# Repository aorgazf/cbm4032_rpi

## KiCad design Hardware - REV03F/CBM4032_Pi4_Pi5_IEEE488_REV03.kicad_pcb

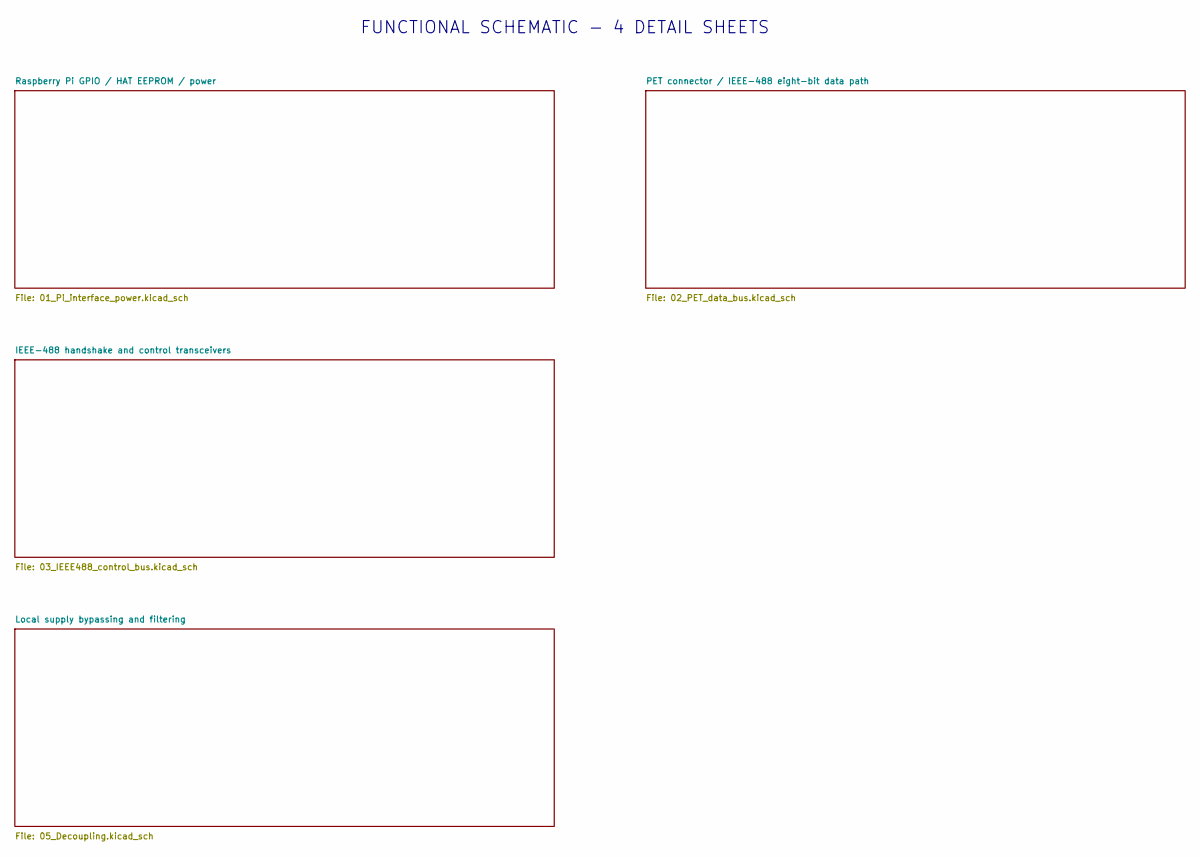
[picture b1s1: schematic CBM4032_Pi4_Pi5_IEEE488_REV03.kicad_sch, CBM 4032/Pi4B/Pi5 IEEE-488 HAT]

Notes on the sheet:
FUNCTIONAL SCHEMATIC - 4 DETAIL SHEETS

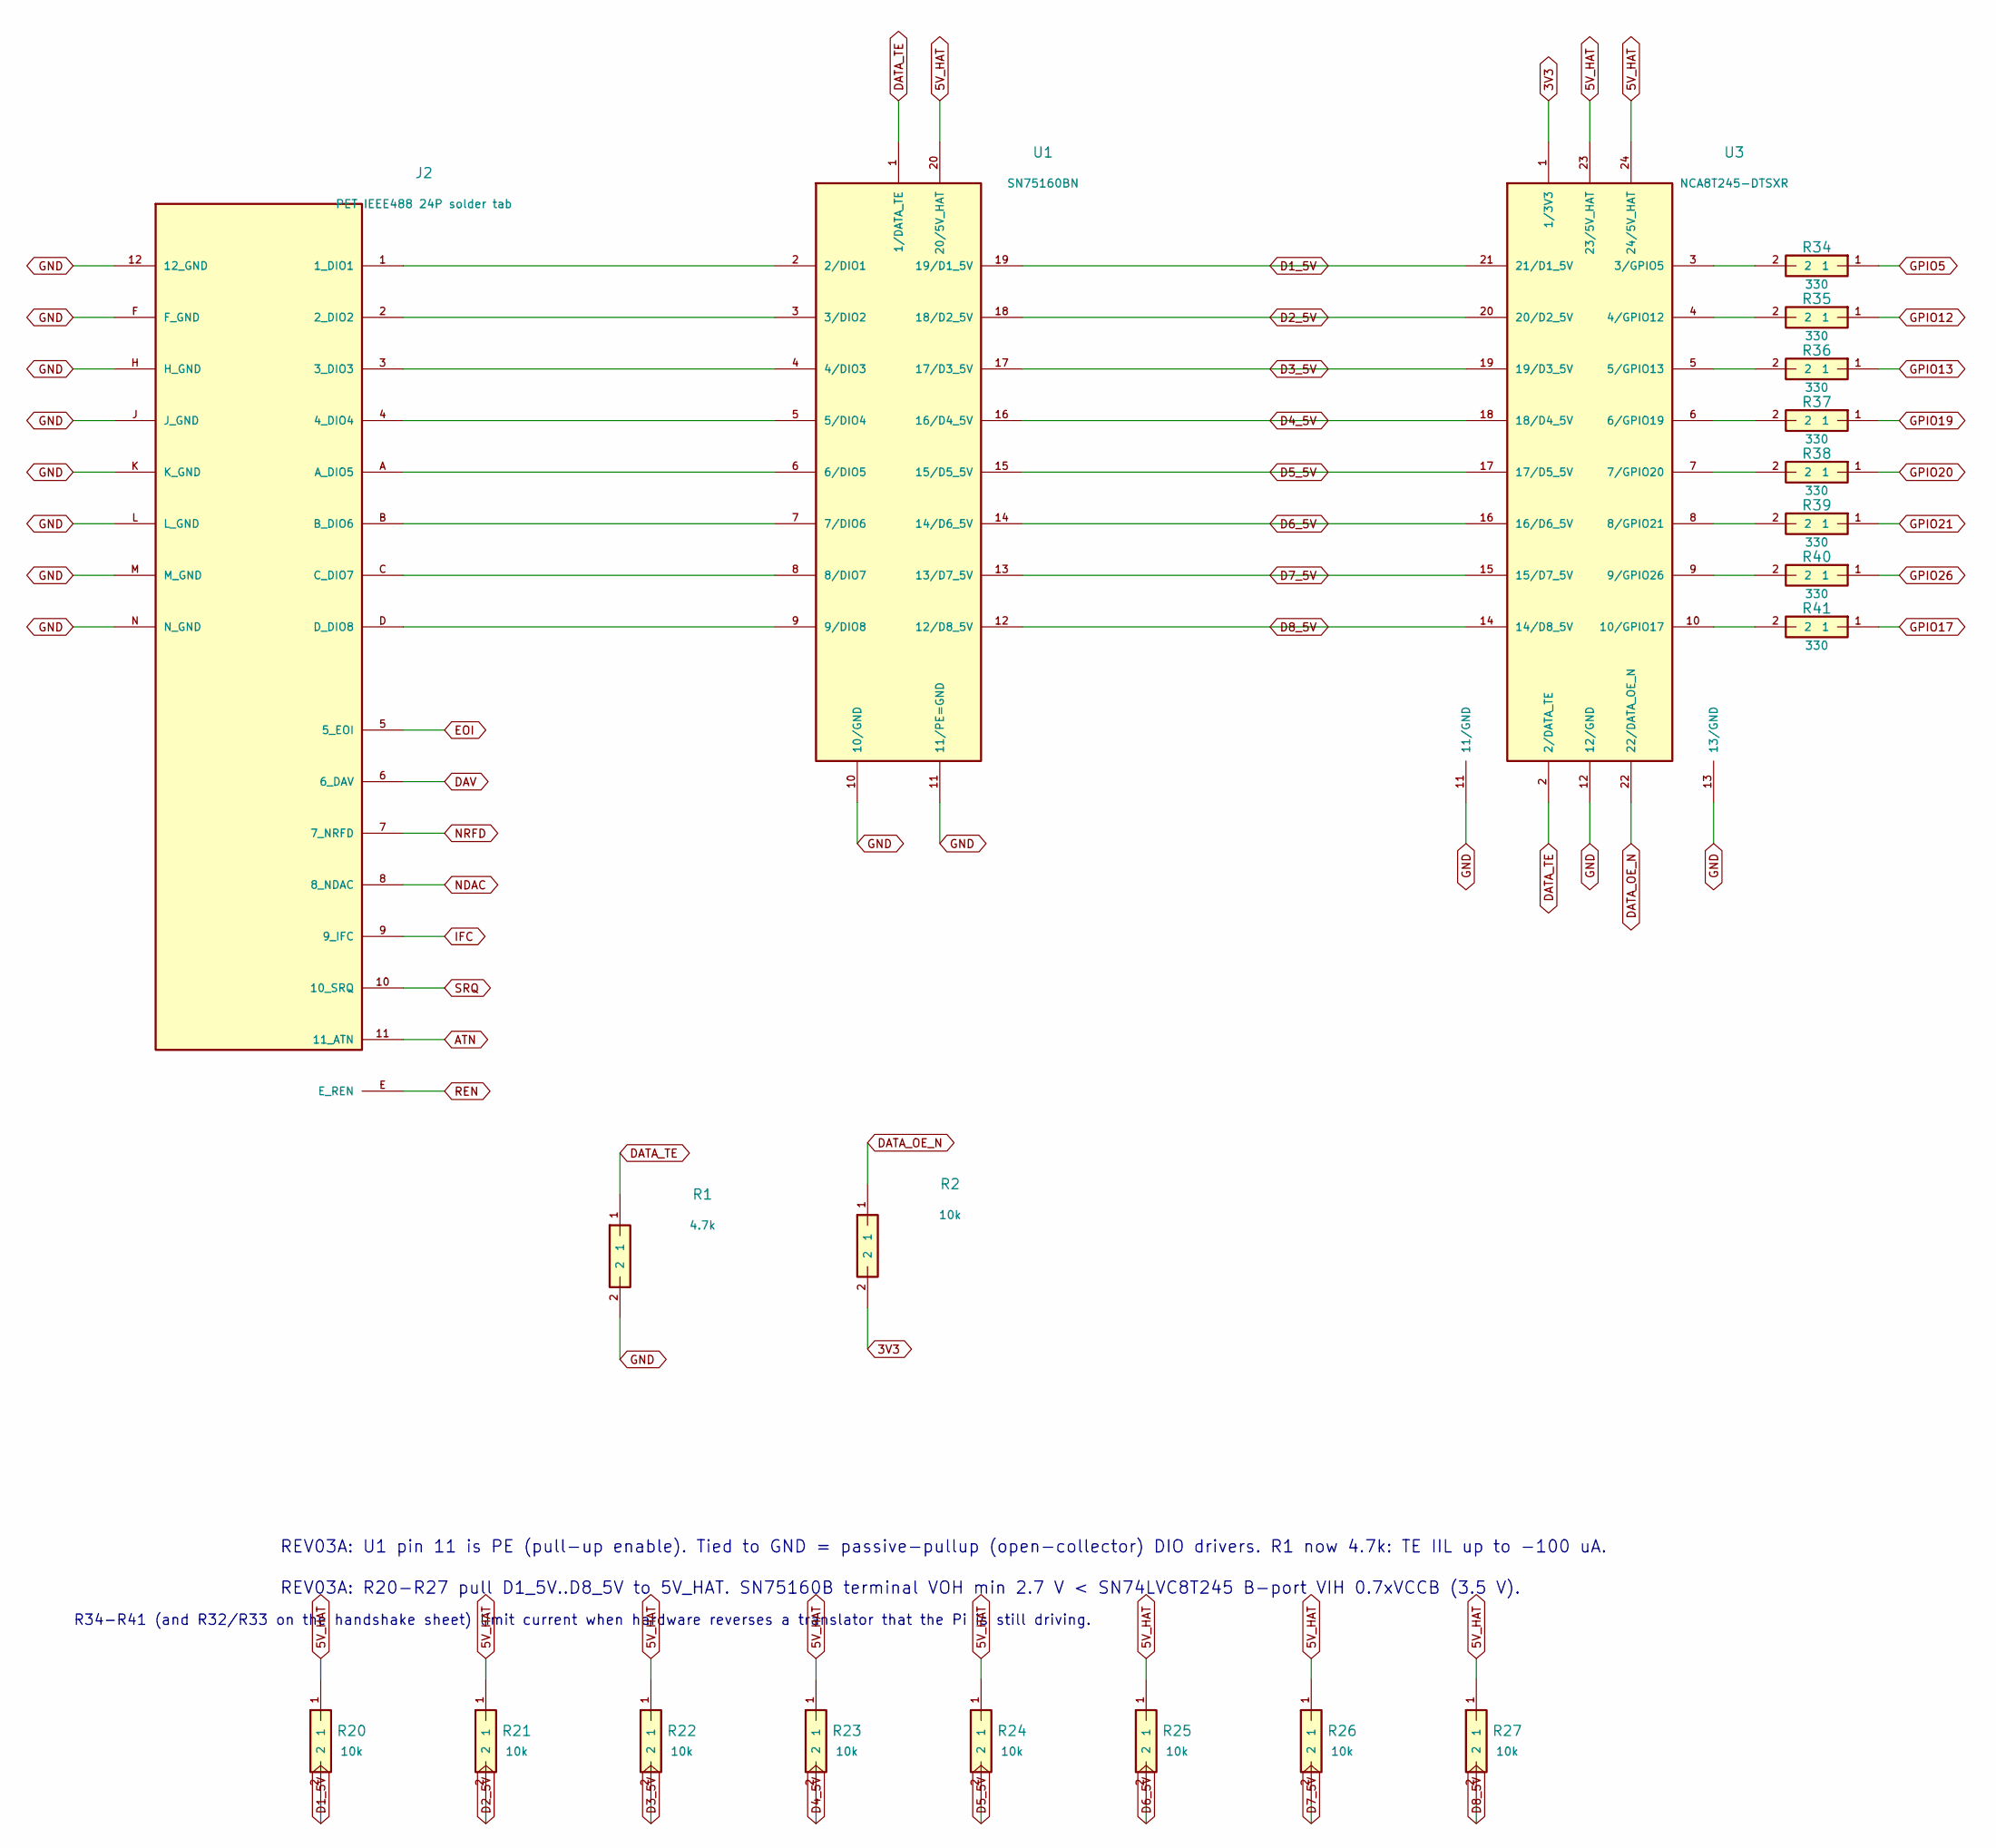
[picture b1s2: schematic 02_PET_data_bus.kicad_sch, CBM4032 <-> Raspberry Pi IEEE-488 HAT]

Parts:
J2: PET IEEE488 24P solder tab; J2
R1: 4.7k; R0805; MPN 0805W8F4701T5E; LCSC C17673
R2, R20, R21, R22, R23, R24, R25, R26, R27: 10k; R0805; MPN 0805W8F1002T5E; LCSC C17414
R34, R35, R36, R37, R38, R39, R40, R41: 330; R0805; MPN 0805W8F3300T5E; LCSC C17630
U1: SN75160BN; DIP20; MPN SN75160BN
U3: NCA8T245-DTSXR; TSSOP24; MPN NCA8T245-DTSXR; LCSC C40086844

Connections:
3V3: R2.2, U3.1 (1/3V3); also elsewhere on the board
5V_HAT: R20.1, R21.1, R22.1, R23.1, R24.1, R25.1, R26.1, R27.1, U1.20 (20/5V_HAT), U3.23 (23/5V_HAT), U3.24 (24/5V_HAT); also elsewhere on the board
ATN: J2.11 (11_ATN); also elsewhere on the board
D1_5V: R20.2, U1.19 (19/D1_5V), U3.21 (21/D1_5V)
D2_5V: R21.2, U1.18 (18/D2_5V), U3.20 (20/D2_5V)
D3_5V: R22.2, U1.17 (17/D3_5V), U3.19 (19/D3_5V)
D4_5V: R23.2, U1.16 (16/D4_5V), U3.18 (18/D4_5V)
D5_5V: R24.2, U1.15 (15/D5_5V), U3.17 (17/D5_5V)
D6_5V: R25.2, U1.14 (14/D6_5V), U3.16 (16/D6_5V)
D7_5V: R26.2, U1.13 (13/D7_5V), U3.15 (15/D7_5V)
D8_5V: R27.2, U1.12 (12/D8_5V), U3.14 (14/D8_5V)
DATA_OE_N: R2.1, U3.22 (22/DATA_OE_N); also elsewhere on the board
DATA_TE: R1.1, U1.1 (1/DATA_TE), U3.2 (2/DATA_TE); also elsewhere on the board
DAV: J2.6 (6_DAV); also elsewhere on the board
EOI: J2.5 (5_EOI); also elsewhere on the board
GND: J2.12 (12_GND), J2.F (F_GND), J2.H (H_GND), J2.J (J_GND), J2.K (K_GND), J2.L (L_GND), J2.M (M_GND), J2.N (N_GND), R1.2, U1.10 (10/GND), U1.11 (11/PE=GND), U3.11 (11/GND), U3.12 (12/GND), U3.13 (13/GND); also elsewhere on the board
GPIO5: R34.1; also elsewhere on the board
GPIO12: R35.1; also elsewhere on the board
GPIO13: R36.1; also elsewhere on the board
GPIO17: R41.1; also elsewhere on the board
GPIO19: R37.1; also elsewhere on the board
GPIO20: R38.1; also elsewhere on the board
GPIO21: R39.1; also elsewhere on the board
GPIO26: R40.1; also elsewhere on the board
IFC: J2.9 (9_IFC); also elsewhere on the board
NDAC: J2.8 (8_NDAC); also elsewhere on the board
NRFD: J2.7 (7_NRFD); also elsewhere on the board
unnamed: J2.1 (1_DIO1), U1.2 (2/DIO1)
unnamed: J2.2 (2_DIO2), U1.3 (3/DIO2)
unnamed: J2.3 (3_DIO3), U1.4 (4/DIO3)
unnamed: J2.4 (4_DIO4), U1.5 (5/DIO4)
unnamed: J2.A (A_DIO5), U1.6 (6/DIO5)
unnamed: J2.B (B_DIO6), U1.7 (7/DIO6)
unnamed: J2.C (C_DIO7), U1.8 (8/DIO7)
unnamed: J2.D (D_DIO8), U1.9 (9/DIO8)
unnamed: R34.2, U3.3 (3/GPIO5)
unnamed: R35.2, U3.4 (4/GPIO12)
unnamed: R36.2, U3.5 (5/GPIO13)
unnamed: R37.2, U3.6 (6/GPIO19)
unnamed: R38.2, U3.7 (7/GPIO20)
unnamed: R39.2, U3.8 (8/GPIO21)
unnamed: R40.2, U3.9 (9/GPIO26)
unnamed: R41.2, U3.10 (10/GPIO17)
REN: J2.E (E_REN); also elsewhere on the board
SRQ: J2.10 (10_SRQ); also elsewhere on the board

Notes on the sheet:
REV03A: R20-R27 pull D1_5V..D8_5V to 5V_HAT. SN75160B terminal VOH min 2.7 V < SN74LVC8T245 B-port VIH 0.7xVCCB (3.5 V).
R34-R41 (and R32/R33 on the handshake sheet) limit current when hardware reverses a translator that the Pi is still driving.
REV03A: U1 pin 11 is PE (pull-up enable). Tied to GND = passive-pullup (open-collector) DIO drivers. R1 now 4.7k: TE IIL up to -100 uA.

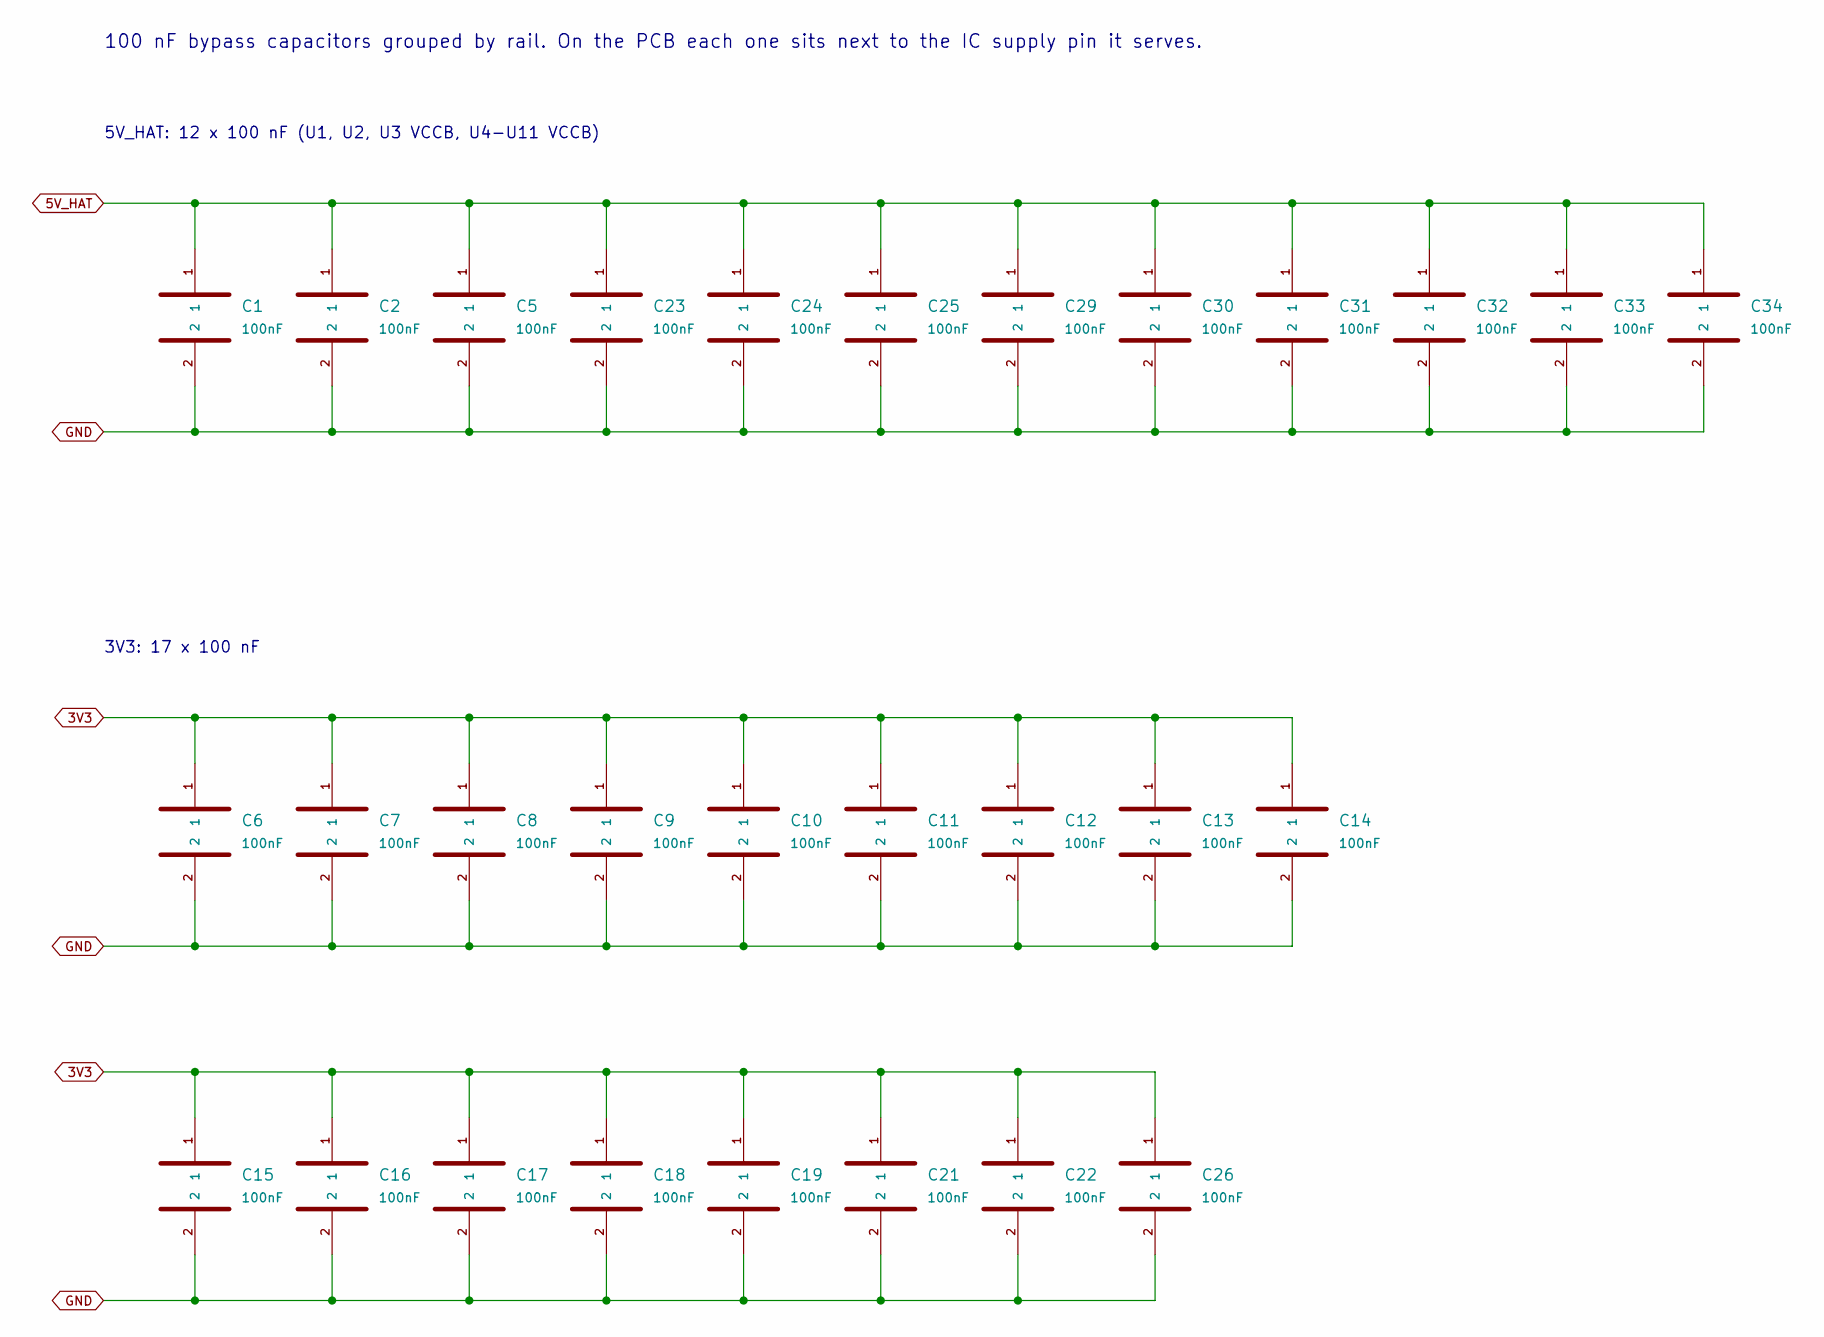
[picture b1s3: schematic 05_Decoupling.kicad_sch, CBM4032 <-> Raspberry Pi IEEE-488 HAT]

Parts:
C1, C2, C5, C6, C7, C8, C9, C10, C11, C12, C13, C14, C15, C16, C17, C18, C19, C21, C22, C23, C24, C25, C26, C29, C30, C31, C32, C33, C34: 100nF; C0805; MPN CC0805KRX7R9BB104; LCSC C49678

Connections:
3V3: C6.1, C7.1, C8.1, C9.1, C10.1, C11.1, C12.1, C13.1, C14.1, C15.1, C16.1, C17.1, C18.1, C19.1, C21.1, C22.1, C26.1; also elsewhere on the board
5V_HAT: C1.1, C2.1, C5.1, C23.1, C24.1, C25.1, C29.1, C30.1, C31.1, C32.1, C33.1, C34.1; also elsewhere on the board
GND: C1.2, C2.2, C5.2, C6.2, C7.2, C8.2, C9.2, C10.2, C11.2, C12.2, C13.2, C14.2, C15.2, C16.2, C17.2, C18.2, C19.2, C21.2, C22.2, C23.2, C24.2, C25.2, C26.2, C29.2, C30.2, C31.2, C32.2, C33.2, C34.2; also elsewhere on the board

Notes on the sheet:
5V_HAT: 12 x 100 nF (U1, U2, U3 VCCB, U4-U11 VCCB)
100 nF bypass capacitors grouped by rail. On the PCB each one sits next to the IC supply pin it serves.
3V3: 17 x 100 nF

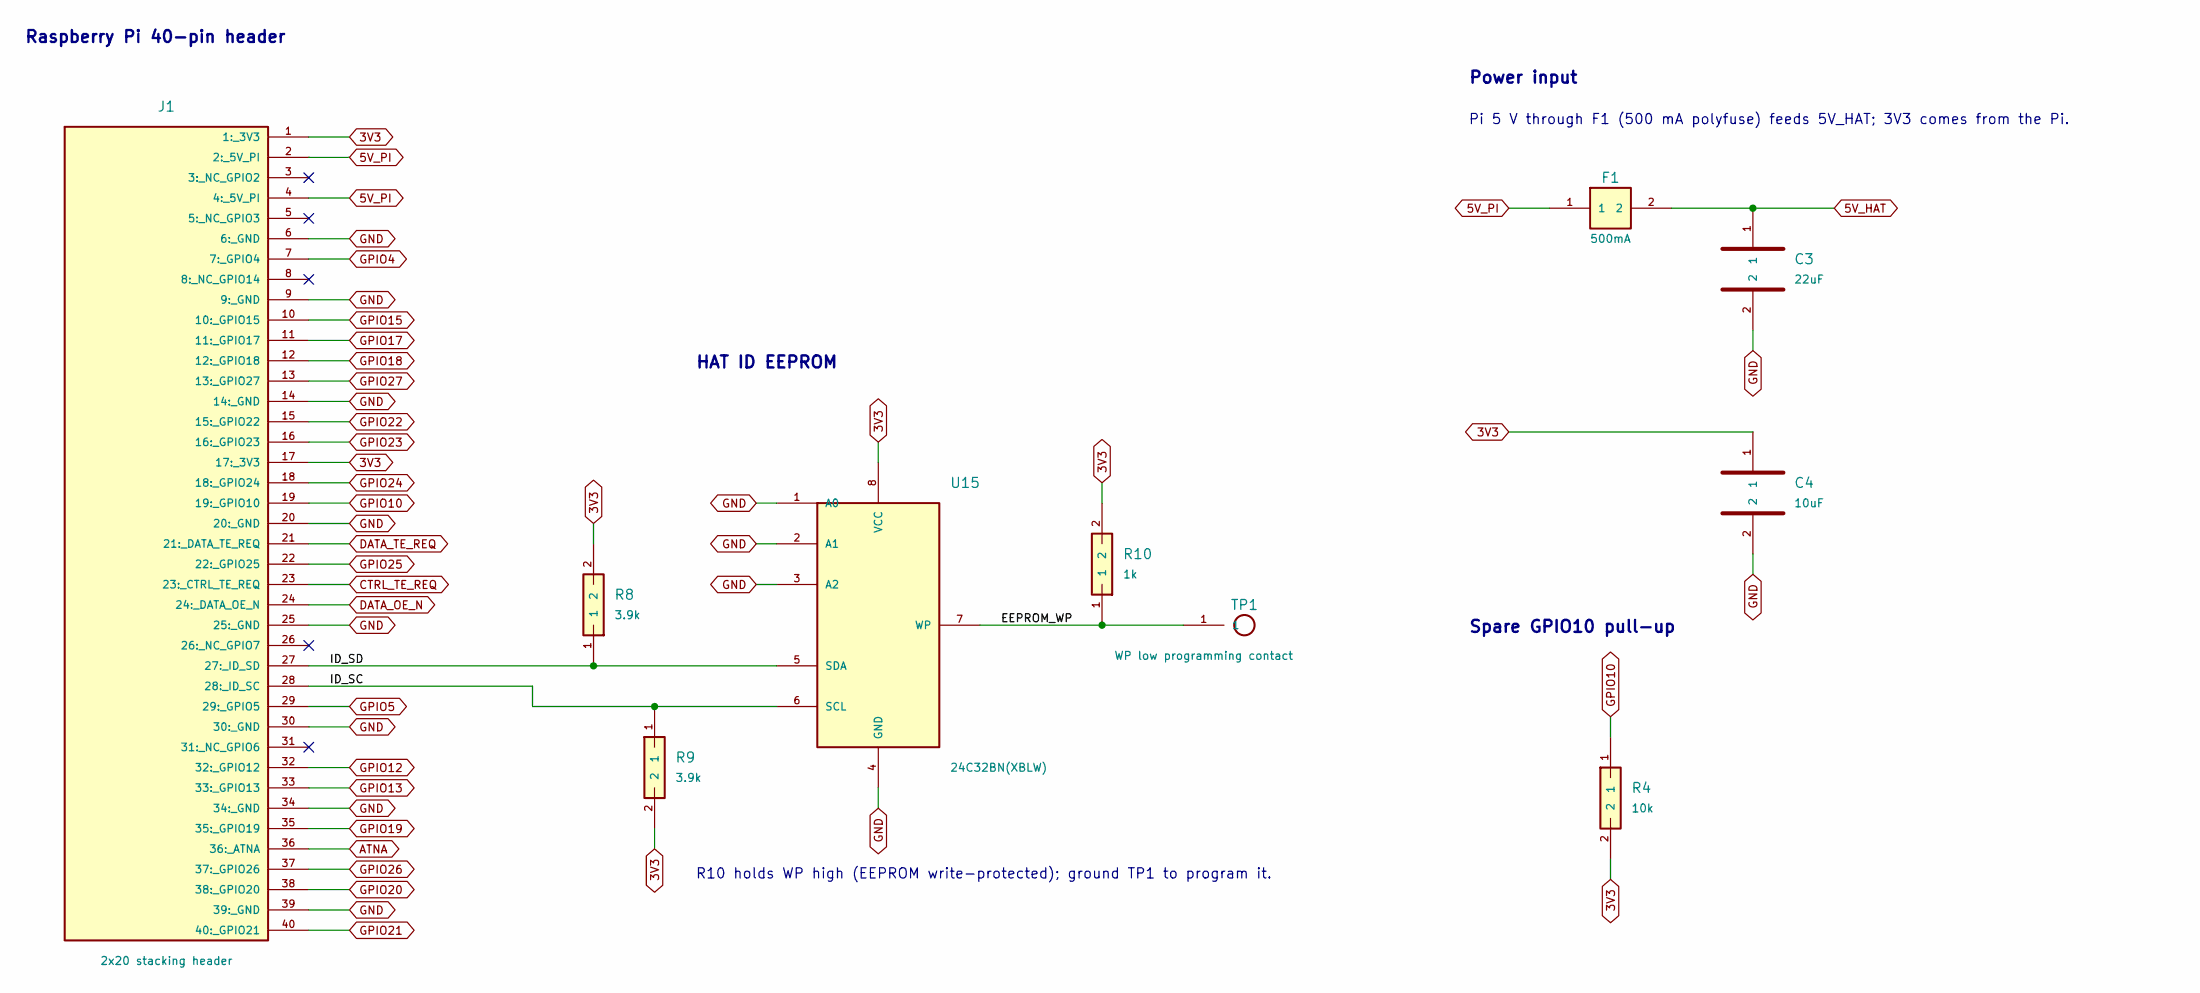
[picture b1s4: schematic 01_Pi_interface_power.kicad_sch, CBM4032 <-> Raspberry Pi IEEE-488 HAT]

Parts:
C3: 22uF; C1206; MPN CL31A226KAHNNNE; LCSC C12891
C4: 10uF; C0805; MPN CL21A106KAYNNNE; LCSC C15850
F1: 500mA; R1206; MPN 1206L050/6NR; LCSC C7542942
J1: 2x20 stacking header; J1
R4: 10k; R0805; MPN 0805W8F1002T5E; LCSC C17414
R8, R9: 3.9k; R0805; MPN 0805W8F3901T5E; LCSC C17614
R10: 1k; R0805; MPN 0805W8F1001T5E; LCSC C17513
TP1: WP low programming contact; TP
U15: 24C32BN(XBLW); SOP8; MPN 24C32BN(XBLW); LCSC C18723546

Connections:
3V3: C4.1, J1.1 (1:_3V3), J1.17 (17:_3V3), R4.2, R8.2, R9.2, R10.2, U15.8 (VCC); also elsewhere on the board
5V_HAT: C3.1, F1.2; also elsewhere on the board
5V_PI: F1.1, J1.2 (2:_5V_PI), J1.4 (4:_5V_PI)
/Raspberry Pi GPIO / HAT EEPROM / power/EEPROM_WP: R10.1, TP1.1 (1_1), U15.7 (WP)
/Raspberry Pi GPIO / HAT EEPROM / power/ID_SC: J1.28 (28:_ID_SC), R9.1, U15.6 (SCL)
/Raspberry Pi GPIO / HAT EEPROM / power/ID_SD: J1.27 (27:_ID_SD), R8.1, U15.5 (SDA)
ATNA: J1.36 (36:_ATNA); also elsewhere on the board
CTRL_TE_REQ: J1.23 (23:_CTRL_TE_REQ); also elsewhere on the board
DATA_OE_N: J1.24 (24:_DATA_OE_N); also elsewhere on the board
DATA_TE_REQ: J1.21 (21:_DATA_TE_REQ); also elsewhere on the board
GND: C3.2, C4.2, J1.6 (6:_GND), J1.9 (9:_GND), J1.14 (14:_GND), J1.20 (20:_GND), J1.25 (25:_GND), J1.30 (30:_GND), J1.34 (34:_GND), J1.39 (39:_GND), U15.1 (A0), U15.2 (A1), U15.3 (A2), U15.4 (GND); also elsewhere on the board
GPIO4: J1.7 (7:_GPIO4); also elsewhere on the board
GPIO5: J1.29 (29:_GPIO5); also elsewhere on the board
GPIO10: J1.19 (19:_GPIO10), R4.1
GPIO12: J1.32 (32:_GPIO12); also elsewhere on the board
GPIO13: J1.33 (33:_GPIO13); also elsewhere on the board
GPIO15: J1.10 (10:_GPIO15); also elsewhere on the board
GPIO17: J1.11 (11:_GPIO17); also elsewhere on the board
GPIO18: J1.12 (12:_GPIO18); also elsewhere on the board
GPIO19: J1.35 (35:_GPIO19); also elsewhere on the board
GPIO20: J1.38 (38:_GPIO20); also elsewhere on the board
GPIO21: J1.40 (40:_GPIO21); also elsewhere on the board
GPIO22: J1.15 (15:_GPIO22); also elsewhere on the board
GPIO23: J1.16 (16:_GPIO23); also elsewhere on the board
GPIO24: J1.18 (18:_GPIO24); also elsewhere on the board
GPIO25: J1.22 (22:_GPIO25); also elsewhere on the board
GPIO26: J1.37 (37:_GPIO26); also elsewhere on the board
GPIO27: J1.13 (13:_GPIO27); also elsewhere on the board

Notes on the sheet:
Pi 5 V through F1 (500 mA polyfuse) feeds 5V_HAT; 3V3 comes from the Pi.
Spare GPIO10 pull-up
R10 holds WP high (EEPROM write-protected); ground TP1 to program it.
Raspberry Pi 40-pin header
Power input
HAT ID EEPROM
